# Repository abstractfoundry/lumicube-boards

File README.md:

# lumicube-boards
PCB and firmware design files for some of the LumiCube components.

Note: this is just for reference. There are probably various broken links to directories along with other issues.

The firmware requires STMCubeIDE. The PCB files require KiCAD.

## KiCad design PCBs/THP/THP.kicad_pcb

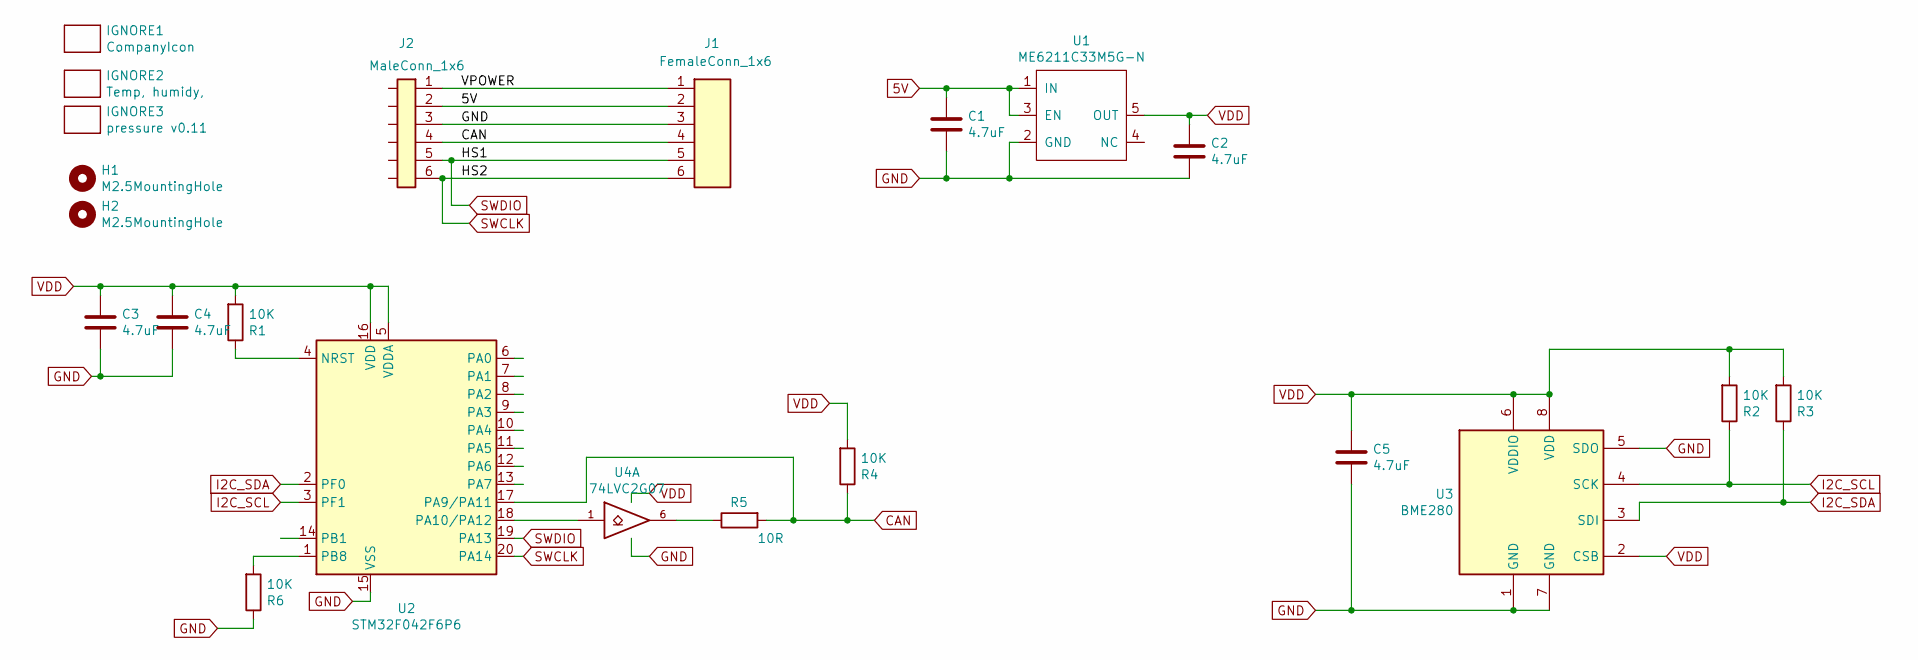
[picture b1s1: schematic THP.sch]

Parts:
C1, C2, C3, C4, C5: 4.7uF; C_0402_1005Metric
H1, H2: M2.5MountingHole; MountingHole_2.7mm_M2.5_ISO7380
IGNORE1: CompanyIcon
IGNORE2: Temp, humidy,; BoardText
IGNORE3: pressure v0.11; BoardText
J1: FemaleConn_1x6; M22-6540642R; Manufacturer_Part_Number A2005HWR-S-6P-Y
J2: MaleConn_1x6; M22-5330605R; Manufacturer_Part_Number A2005WR-S-6P
R1, R2, R3, R4, R6: 10K; R_0402_1005Metric
R5: 10R; R_0402_1005Metric
U1: ME6211C33M5G-N; SOT-23-5
U2: STM32F042F6P6
U3: BME280; TempHumidyPressure_BME280; Manufacturer_Part_Number BME280
U4: 74LVC2G07; SOT-23-6

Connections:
5V: C1.1, J1.2, J2.2, U1.1 (IN), U1.3 (EN)
/VPOWER: J1.1, J2.1
CAN: J1.4, J2.4, R4.1, R5.2, U2.17 (PA9/PA11)
GND: C1.2, C2.2, C3.2, C4.2, C5.2, J1.3, J2.3, R6.1, U1.2 (GND), U2.15 (VSS), U3.1 (GND), U3.5 (SDO), U3.7 (GND), U4.2 (GND)
I2C_SCL: R2.1, U2.3 (PF1), U3.4 (SCK)
I2C_SDA: R3.1, U2.2 (PF0), U3.3 (SDI)
unnamed: R1.1, U2.4 (NRST)
unnamed: R5.1, U4.6
unnamed: R6.2, U2.1 (PB8)
unnamed: U2.18 (PA10/PA12), U4.1
SWCLK: J1.6, J2.6, U2.20 (PA14)
SWDIO: J1.5, J2.5, U2.19 (PA13)
VDD: C2.1, C3.1, C4.1, C5.1, R1.2, R2.2, R3.2, R4.2, U1.5 (OUT), U2.5 (VDDA), U2.16 (VDD), U3.2 (CSB), U3.6 (VDDIO), U3.8 (VDD), U4.5 (VCC)

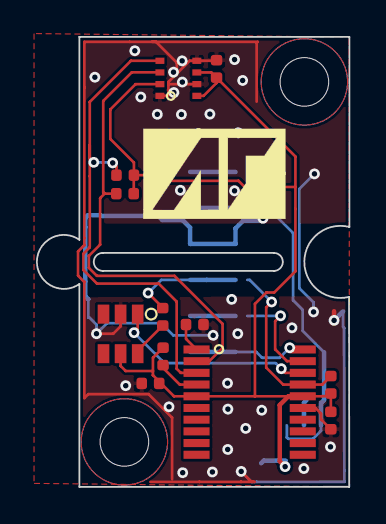
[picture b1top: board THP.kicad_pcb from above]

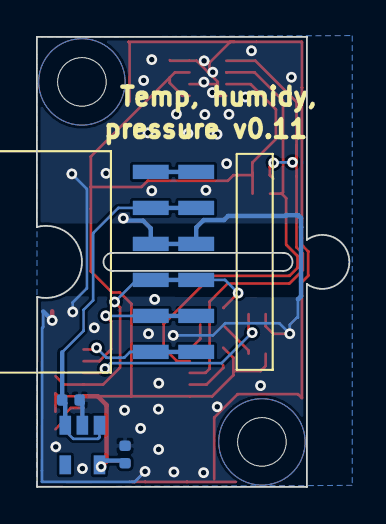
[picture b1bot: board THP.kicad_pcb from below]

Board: 2 copper layers, 17.4 x 25.0 mm, 22 parts (5 on the bottom side), 13 nets.

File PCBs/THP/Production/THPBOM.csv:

References,Value,Quantity,Type,Manufacturer,Manufacturer_Part_Number,THT,Number_of_pads,Can be replaced,Notes,LCSC_part_number,Link
"C4,C5,C3,C1,C2",4.7uF,5,Capacitor,Samsung,CL05A475MP5NRNC,N,2,N,,C23733,https://lcsc.com/product-detail/Multilayer-Ceramic-Capacitor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
J1,FemaleConn_1x6,1,Connector,Changjiang Connectors,A2005HWR-S-6P-Y,N,6,Y,,,https://www.cjt.com/en/pro_show.php?id=15894
J2,MaleConn_1x6,1,Connector,Changjiang Connectors,A2005WR-S-6P,N,6,Y,,C917593,https://www.cjt.com/en/pro_show.php?id=15952
R5,10R,1,Resistor,,,N,2,Y,0402,C25077,
"R6,R3,R2,R1,R4",10K,5,Resistor,,,N,2,Y,0402,C25744,
U1,ME6211C33M5G-N,1,IC,Nanjing Micro One Elec,ME6211C33M5G-N,N,3,N,,C82942,https://lcsc.com/product-detail/Linear-Voltage-Regulators-LD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
U2,STM32F042F6P6,1,IC,STMicroelectronics,STM32F042F6P6,N,20,N,,C81000,https://lcsc.com/product-detail/ST-Microelectronics_STMicroe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
U3,BME280,1,IC,Bosch Sensortec ,BME280,N,8,N,,C92489,https://lcsc.com/product-detail/Humidity-Sensors_Bosch-Senso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
U4,74LVC2G07,1,IC,Texas Instruments,SN74LVC2G07DBVR,N,6,N,,C37708,https://lcsc.com/product-detail/Buffers-Drivers_Texas-Instru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

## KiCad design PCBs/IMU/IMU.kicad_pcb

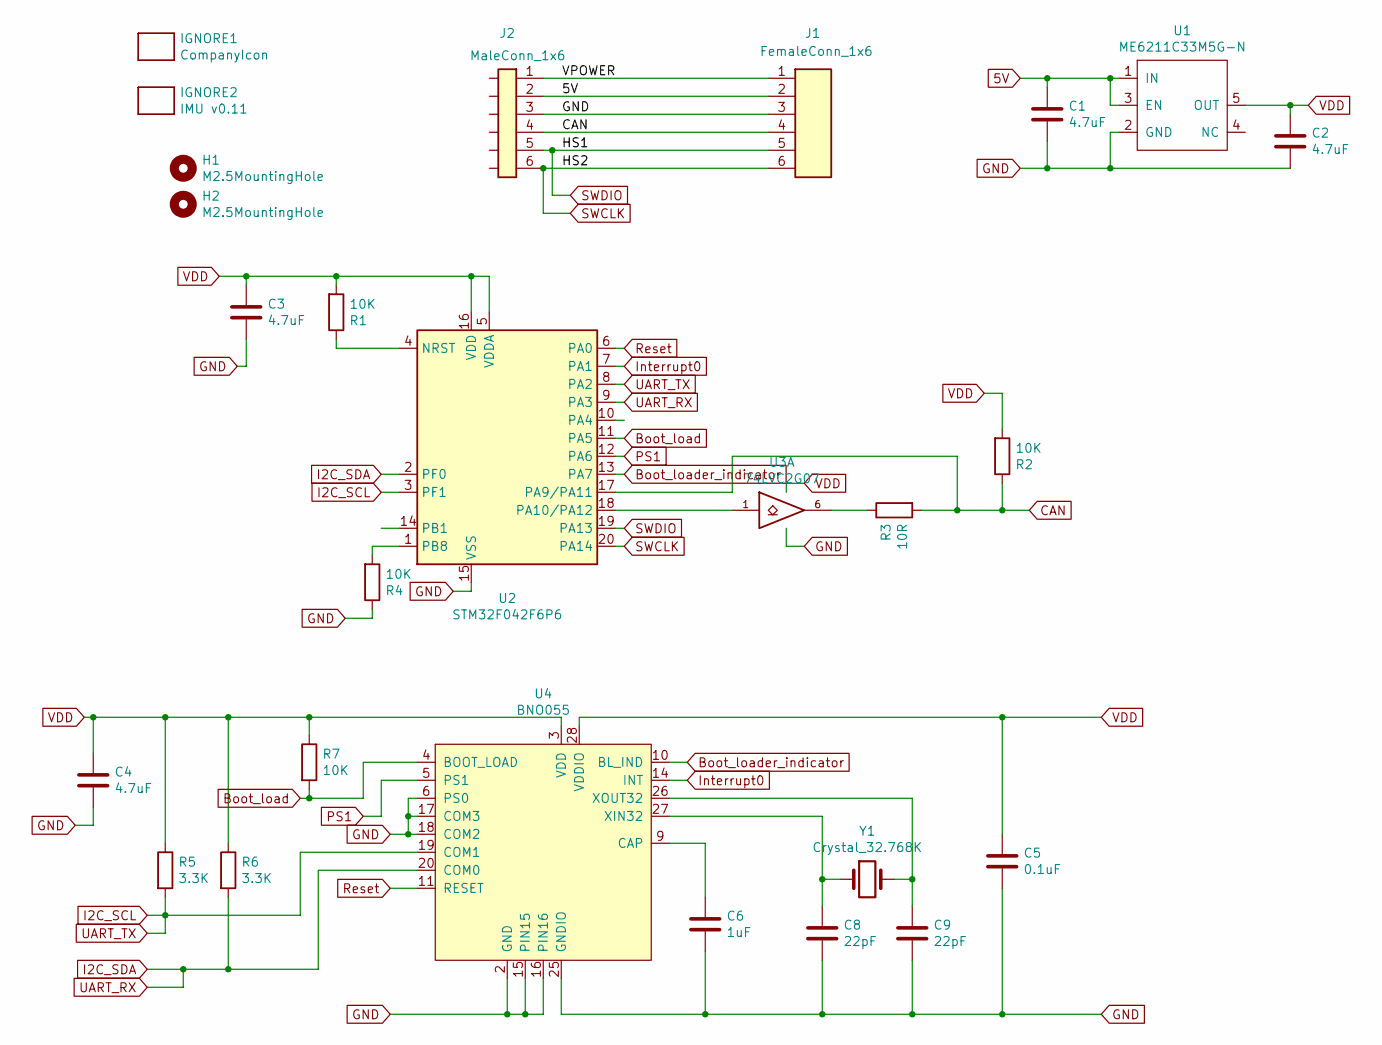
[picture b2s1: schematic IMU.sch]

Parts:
C1, C2, C3, C4: 4.7uF; C_0402_1005Metric
C5: 0.1uF; C_0402_1005Metric
C6: 1uF; C_0402_1005Metric
C8, C9: 22pF; C_0402_1005Metric
H1, H2: M2.5MountingHole; MountingHole_2.7mm_M2.5_ISO7380
IGNORE1: CompanyIcon
IGNORE2: IMU v0.11; BoardText
J1: FemaleConn_1x6; M22-6540642R; Manufacturer_Part_Number A2005HWR-S-6P-Y
J2: MaleConn_1x6; M22-5330605R; Manufacturer_Part_Number A2005WR-S-6P
R1, R2, R4, R7: 10K; R_0402_1005Metric
R3: 10R; R_0402_1005Metric
R5, R6: 3.3K; R_0402_1005Metric
U1: ME6211C33M5G-N; SOT-23-5
U2: STM32F042F6P6
U3: 74LVC2G07; SOT-23-6
U4: BNO055; IMU-BNO055; Manufacturer_Part_Number BNO055
Y1: Crystal_32.768K; Crystal_SMD_3215-2Pin_3.2x1.5mm

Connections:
5V: C1.1, J1.2, J2.2, U1.1 (IN), U1.3 (EN)
/VPOWER: J1.1, J2.1
Boot_load: R7.2, U2.11 (PA5), U4.4 (BOOT_LOAD)
Boot_loader_indicator: U2.13 (PA7), U4.10 (BL_IND)
CAN: J1.4, J2.4, R2.1, R3.2, U2.17 (PA9/PA11)
GND: C1.2, C2.2, C3.2, C4.2, C5.2, C6.2, C8.2, C9.2, J1.3, J2.3, R4.1, U1.2 (GND), U2.15 (VSS), U3.2 (GND), U4.2 (GND), U4.6 (PS0), U4.15 (PIN15), U4.16 (PIN16), U4.17 (COM3), U4.18 (COM2), U4.25 (GNDIO)
I2C_SCL: R5.2, U2.3 (PF1), U2.8 (PA2), U4.19 (COM1)
I2C_SDA: R6.2, U2.2 (PF0), U2.9 (PA3), U4.20 (COM0)
Interrupt0: U2.7 (PA1), U4.14 (INT)
unnamed: C6.1, U4.9 (CAP)
unnamed: C8.1, U4.27 (XIN32), Y1.1
unnamed: C9.1, U4.26 (XOUT32), Y1.2
unnamed: R1.1, U2.4 (NRST)
unnamed: R3.1, U3.6
unnamed: R4.2, U2.1 (PB8)
unnamed: U2.18 (PA10/PA12), U3.1
PS1: U2.12 (PA6), U4.5 (PS1)
Reset: U2.6 (PA0), U4.11 (RESET)
SWCLK: J1.6, J2.6, U2.20 (PA14)
SWDIO: J1.5, J2.5, U2.19 (PA13)
VDD: C2.1, C3.1, C4.1, C5.1, R1.2, R2.2, R5.1, R6.1, R7.1, U1.5 (OUT), U2.5 (VDDA), U2.16 (VDD), U3.5 (VCC), U4.3 (VDD), U4.28 (VDDIO)

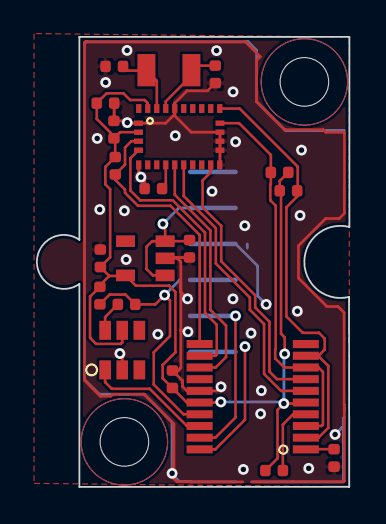
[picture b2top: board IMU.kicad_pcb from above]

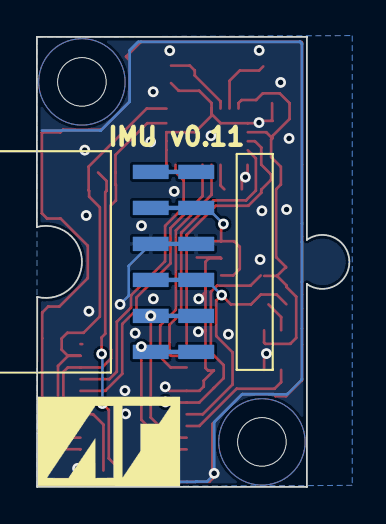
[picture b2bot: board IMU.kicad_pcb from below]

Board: 2 copper layers, 17.4 x 25.0 mm, 26 parts (3 on the bottom side), 21 nets.

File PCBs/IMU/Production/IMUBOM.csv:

References,Value,Quantity,Type,Manufacturer,Manufacturer_Part_Number,THT,Number_of_pads,Can be replaced,Notes,LCSC_part_number,Link
"C4,C3,C1,C2",4.7uF,4,Capacitor,Samsung,CL05A475MP5NRNC,N,2,N,,C23733,https://lcsc.com/product-detail/Multilayer-Ceramic-Capacitor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
C5,0.1uF,1,Capacitor,Samsung,CL05B104KO5NNNC,N,2,N,,C1525,https://lcsc.com/product-detail/Multilayer-Ceramic-Capacitor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
C6,1uF,1,Capacitor,Samsung,CL05A105KA5NQNC,N,2,Y,,C52923,https://lcsc.com/product-detail/Multilayer-Ceramic-Capacitor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
"C8,C9",22pF,2,Capacitor,Samsung,CL05C220JB5NNNC,N,2,Y,,C70464,https://lcsc.com/product-detail/Multilayer-Ceramic-Capacitor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
J1,FemaleConn_1x6,1,Connector,Changjiang Connectors,A2005HWR-S-6P-Y,N,6,Y,,,https://www.cjt.com/en/pro_show.php?id=15894
J2,MaleConn_1x6,1,Connector,Changjiang Connectors,A2005WR-S-6P,N,6,Y,,C917593,https://www.cjt.com/en/pro_show.php?id=15952
R3,10R,1,Resistor,,,N,2,Y,0402,C25077,
"R4,R1,R7,R2",10K,4,Resistor,,,N,2,Y,0402,C25744,
"R6,R5",3.3K,2,Resistor,,,N,2,Y,0402,C25890,
U1,ME6211C33M5G-N,1,IC,Nanjing Micro One Elec,ME6211C33M5G-N,N,3,N,,C82942,https://lcsc.com/product-detail/Linear-Voltage-Regulators-LD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
U2,STM32F042F6P6,1,IC,STMicroelectronics,STM32F042F6P6,N,20,N,,C81000,https://lcsc.com/product-detail/ST-Microelectronics_STMicroe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
U3,74LVC2G07,1,IC,Texas Instruments,SN74LVC2G07DBVR,N,6,N,,C37708,https://lcsc.com/product-detail/Buffers-Drivers_Texas-Instru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
U4,BNO055,1,IC,Bosch,BNO055,N,28,N,,C93216,https://lcsc.com/product-detail/Sensors_Bosch-Sensortec_BNO0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
Y1,Crystal_32.768K,1,Crystal,JGHC,SMD31327681252090,N,2,N,,C390740,https://lcsc.com/product-detail/SMD-Crystal-Resonators_JGHC-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

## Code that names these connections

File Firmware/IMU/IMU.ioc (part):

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Mcu.Name=STM32F042F6Px
Mcu.Package=TSSOP20
Mcu.UserName=STM32F042F6Px
PA0.Signal=GPIO_Output
PA1.Signal=GPIO_Input
PA11.Mode=CAN_Activate
PA11.Signal=CAN_RX
PA12.Mode=CAN_Activate
PA12.Signal=CAN_TX
PA13.Mode=Serial_Wire
PA13.Signal=SYS_SWDIO
PA14.Mode=Serial_Wire
PA14.Signal=SYS_SWCLK
PA2.Mode=Asynchronous
PA2.Signal=USART2_TX
PA3.Mode=Asynchronous
PA3.Signal=USART2_RX
PA5.Signal=GPIO_Output
PA6.Signal=GPIO_Output
PA7.Signal=GPIO_Input
PF0-OSC_IN.Mode=I2C
PF0-OSC_IN.Signal=I2C1_SDA
PF1-OSC_OUT.Mode=I2C
PF1-OSC_OUT.Signal=I2C1_SCL
RCC.SYSCLKFreq_VALUE=48000000
RCC.SYSCLKSource=RCC_SYSCLKSOURCE_PLLCLK
board=custom

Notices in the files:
PCBs/IMU/IMU.sch:
Copyright (c) 2020 Abstract Foundry Limited
